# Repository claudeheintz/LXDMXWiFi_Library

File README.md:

# LXDMXWiFi_library
Library for ESP8266 implements Art-Net and sACN with example sketches showing both DMX input to and DMX output from network.

LXDMXWiFi encapsulates functionality for sending and receiving DMX over an ESP8266 WiFi connection
   It is a virtual class with concrete subclasses LXWiFiArtNet and LXWiFiSACN which specifically
   implement the Artistic Licence Art-Net and PLASA sACN 1.31 protocols.

Included examples of the library's use:

         DMX input to network using UART and MAX485 driver chip

         Test of receiving two universes of DMX data from network

         DMX output from network using UART and MAX485 driver chip
            This example includes Eagle files and photos of completed project using this example
            It also includes python script for remote management of protocol/wifi settings
            
Photo shows complete WiFi to DMX unit with RJ45 connector for DMX output: (not to be confused with ethernet)

On the left side is connector for external 5v power and default boot push button.  (holding down default boot forces unit into access point mode allowing configuration via network using python tool.)

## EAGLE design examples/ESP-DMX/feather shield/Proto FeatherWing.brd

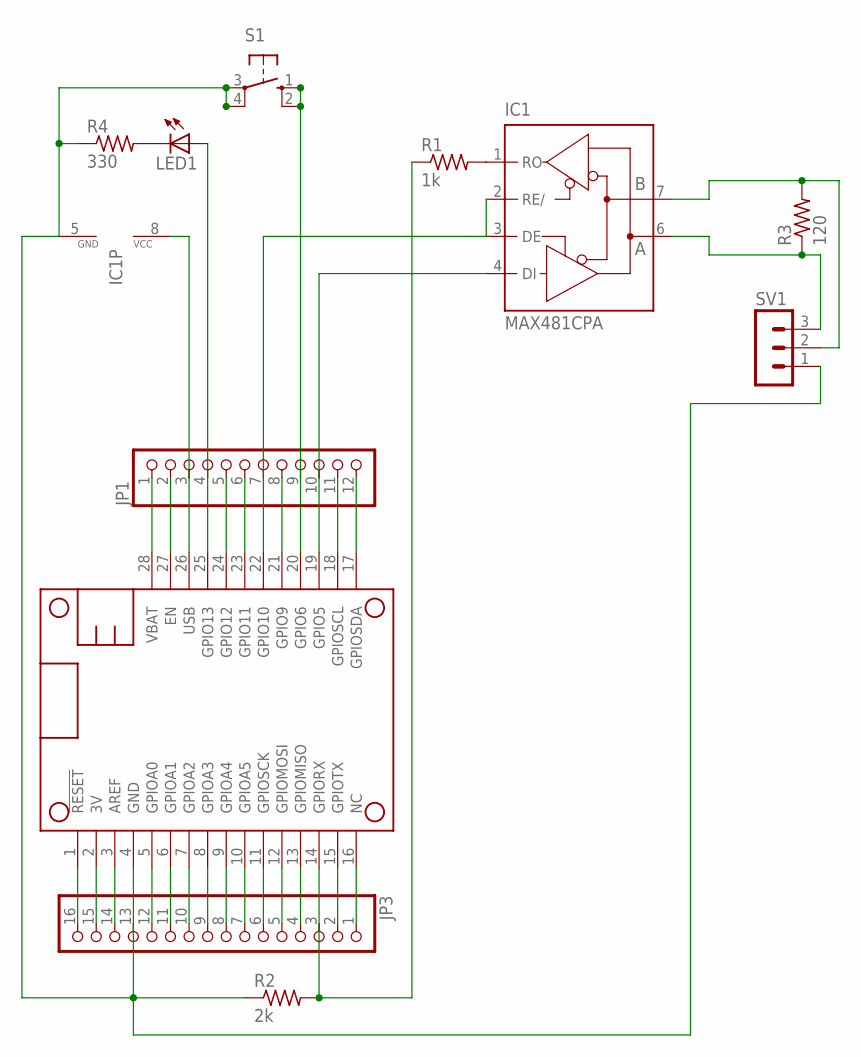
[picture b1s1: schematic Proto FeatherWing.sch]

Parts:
IC1: MAX481CPA; DIL08
JP1: HEADER-1X1276MIL; 1X12_ROUND_76MIL
JP3: HEADER-1X16_76MIL; 1X16_ROUND_76MIL
LED1: LED5MM
MS1: FEATHERWING
R1: 1k; 0204/5
R2: 2k; 0204/5
R3: 120; 0204/5
R4: 330; 0204/5
S1: 10-XX; B3F-10XX
SV1: MA03-1

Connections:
3V: JP3.15, MS1.2 (3V)
AREF: JP3.14, MS1.3 (AREF)
unnamed: JP1.2, MS1.27 (EN)
unnamed: JP3.1, MS1.16 (NC)
unnamed: JP1.4, LED1.A, MS1.25 (GPIO13)
unnamed: JP3.2, MS1.15 (GPIOTX)
unnamed: JP1.5, MS1.24 (GPIO12)
unnamed: JP3.3, MS1.14 (GPIORX), R1.1, R2.2
unnamed: JP3.4, MS1.13 (GPIOMISO)
unnamed: JP3.5, MS1.12 (GPIOMOSI)
unnamed: JP3.6, MS1.11 (GPIOSCK)
unnamed: JP3.7, MS1.10 (GPIOA5)
unnamed: JP3.8, MS1.9 (GPIOA4)
unnamed: JP3.9, MS1.8 (GPIOA3)
unnamed: JP3.10, MS1.7 (GPIOA2)
unnamed: JP3.11, MS1.6 (GPIOA1)
unnamed: JP3.12, MS1.5 (GPIOA0)
unnamed: IC1.1 (RO), R1.2
unnamed: IC1.6 (A), R3.1, SV1.3
unnamed: JP3.16, MS1.1 (!RESET)
unnamed: JP1.6, MS1.23 (GPIO11)
unnamed: IC1.4 (DI), JP1.10, MS1.19 (GPIO5)
unnamed: JP1.8, MS1.21 (GPIO9)
unnamed: JP1.9, MS1.20 (GPIO6), S1.1 (S), S1.2 (S1)
unnamed: LED1.K (C), R4.2
unnamed: JP1.11, MS1.18 (GPIOSCL)
unnamed: JP1.12, MS1.17 (GPIOSDA)
unnamed: IC1.5 (GND), JP3.13, MS1.4 (GND), R2.1, R4.1, S1.3, S1.4 (P1), SV1.1
unnamed: IC1.7 (B), R3.2, SV1.2
unnamed: IC1.2 (RE/), IC1.3 (DE), JP1.7, MS1.22 (GPIO10)
USB: IC1.8 (VCC), JP1.3, MS1.26 (USB)
VBAT: JP1.1, MS1.28 (VBAT)

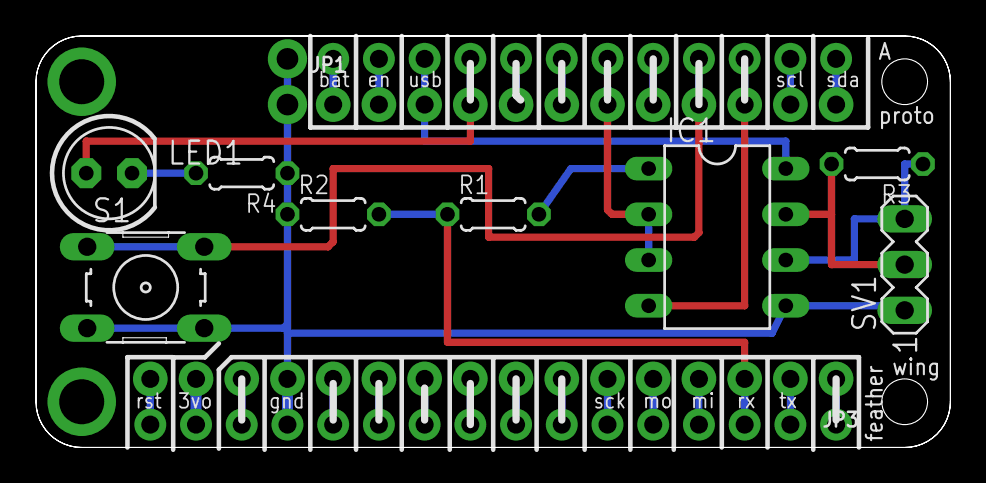
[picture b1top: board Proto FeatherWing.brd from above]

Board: 2 copper layers, 50.8 x 22.9 mm, 11 parts (0 on the bottom side), 32 nets.

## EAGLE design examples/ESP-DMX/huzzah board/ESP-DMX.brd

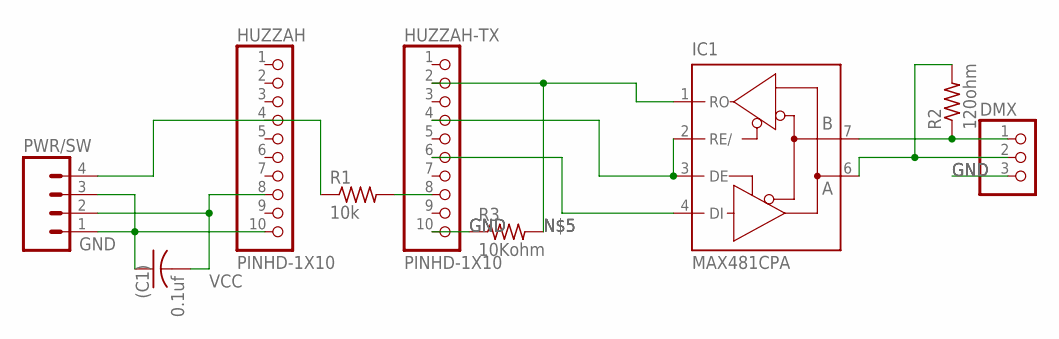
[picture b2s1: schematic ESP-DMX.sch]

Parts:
(C1): 0.1uf; C050-025X075
DMX: PINHD-1X3; 1X03
HUZZAH: PINHD-1X10; 1X10-BIG
HUZZAH-TX: PINHD-1X10; 1X10-BIG
IC1: MAX481CPA; DIL08
PWR/SW: 1X04_HEADER"; 1X04_HEADER
R1: 10k; RESISTOR
R2: 120ohm; RESISTOR
R3: 10Kohm; RESISTOR

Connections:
GND: (C1).1, DMX.3, HUZZAH.10, HUZZAH-TX.10, IC1.5 (GND), PWR/SW.1, PWR/SW.3, R3.1
unnamed: DMX.1, IC1.7 (B), R2.1
unnamed: DMX.2, IC1.6 (A), R2.2
unnamed: HUZZAH-TX.6, IC1.4 (DI)
unnamed: HUZZAH-TX.4, IC1.2 (RE/), IC1.3 (DE)
unnamed: HUZZAH-TX.2, IC1.1 (RO), R3.2
unnamed: HUZZAH-TX.8, R1.2
unnamed: HUZZAH.4, PWR/SW.4, R1.1
VCC: (C1).2, HUZZAH.8, IC1.8 (VCC), PWR/SW.2

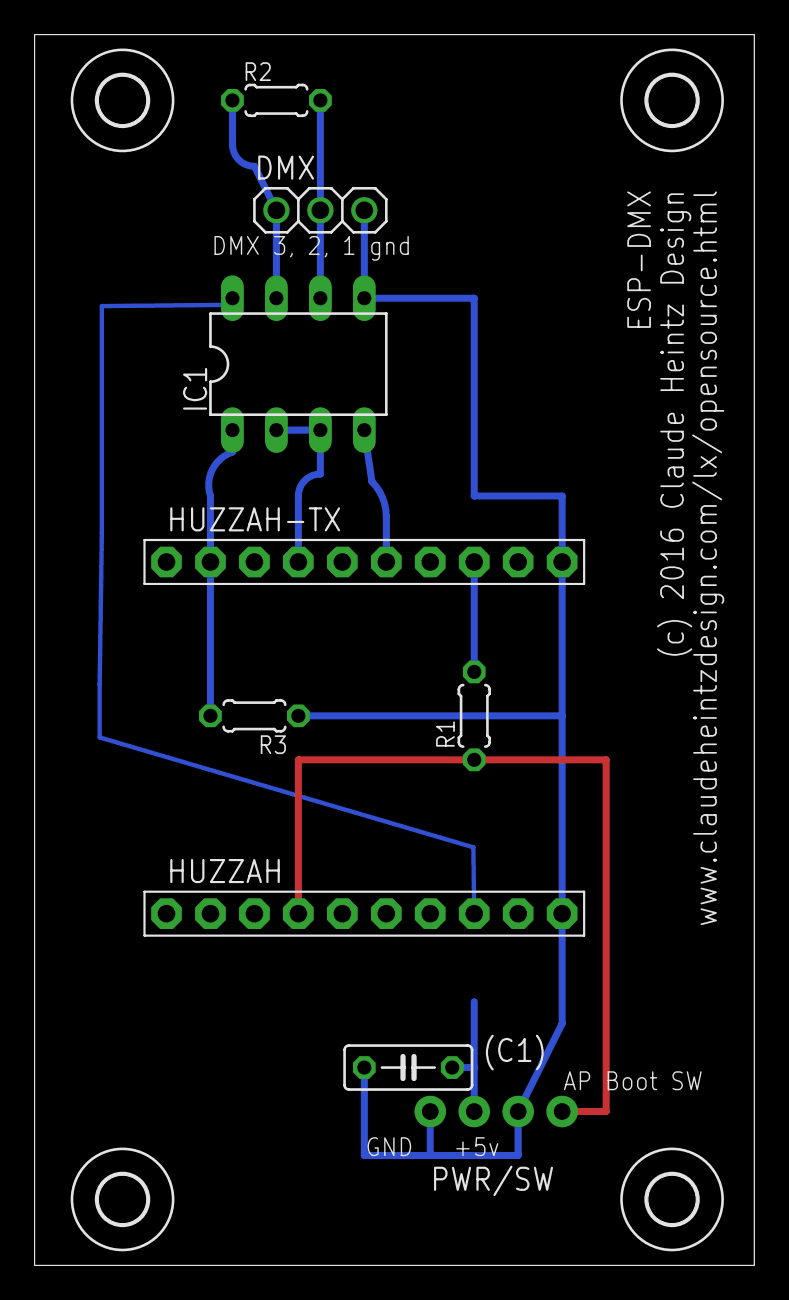
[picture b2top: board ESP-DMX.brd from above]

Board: 2 copper layers, 41.6 x 71.1 mm, 13 parts (0 on the bottom side), 9 nets.

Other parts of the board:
U$3, U$4, U$5, U$6: 2,8

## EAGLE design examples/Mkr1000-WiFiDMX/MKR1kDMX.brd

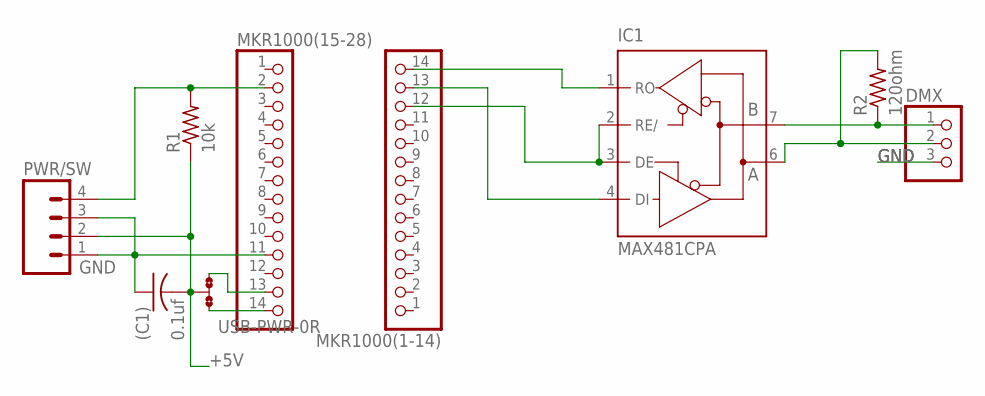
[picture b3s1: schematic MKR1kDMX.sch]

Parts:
(C1): 0.1uf; C050-025X075
DMX: PINHD-1X3; 1X03
IC1: MAX481CPA; DIL08
MKR1000(1-14), MKR1000(15-28): PINHD-1X14; 1X14
PWR/SW: 1X04_HEADER"; 1X04_HEADER
R1: 10k; RESISTOR
R2: 120ohm; RESISTOR
USB-PWR: PWR-IN; B0R-JMP

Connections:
+5V: (C1).2, IC1.8 (VCC), PWR/SW.2, R1.1, USB-PWR.2
GND: (C1).1, DMX.3, IC1.5 (GND), MKR1000(15-28).11, PWR/SW.1, PWR/SW.3
unnamed: DMX.1, IC1.7 (B), R2.1
unnamed: DMX.2, IC1.6 (A), R2.2
unnamed: IC1.4 (DI), MKR1000(1-14).13
unnamed: IC1.2 (RE/), IC1.3 (DE), MKR1000(1-14).12
unnamed: IC1.1 (RO), MKR1000(1-14).14
unnamed: MKR1000(15-28).2, PWR/SW.4, R1.2
unnamed: MKR1000(15-28).13, USB-PWR.3
unnamed: MKR1000(15-28).14, USB-PWR.1

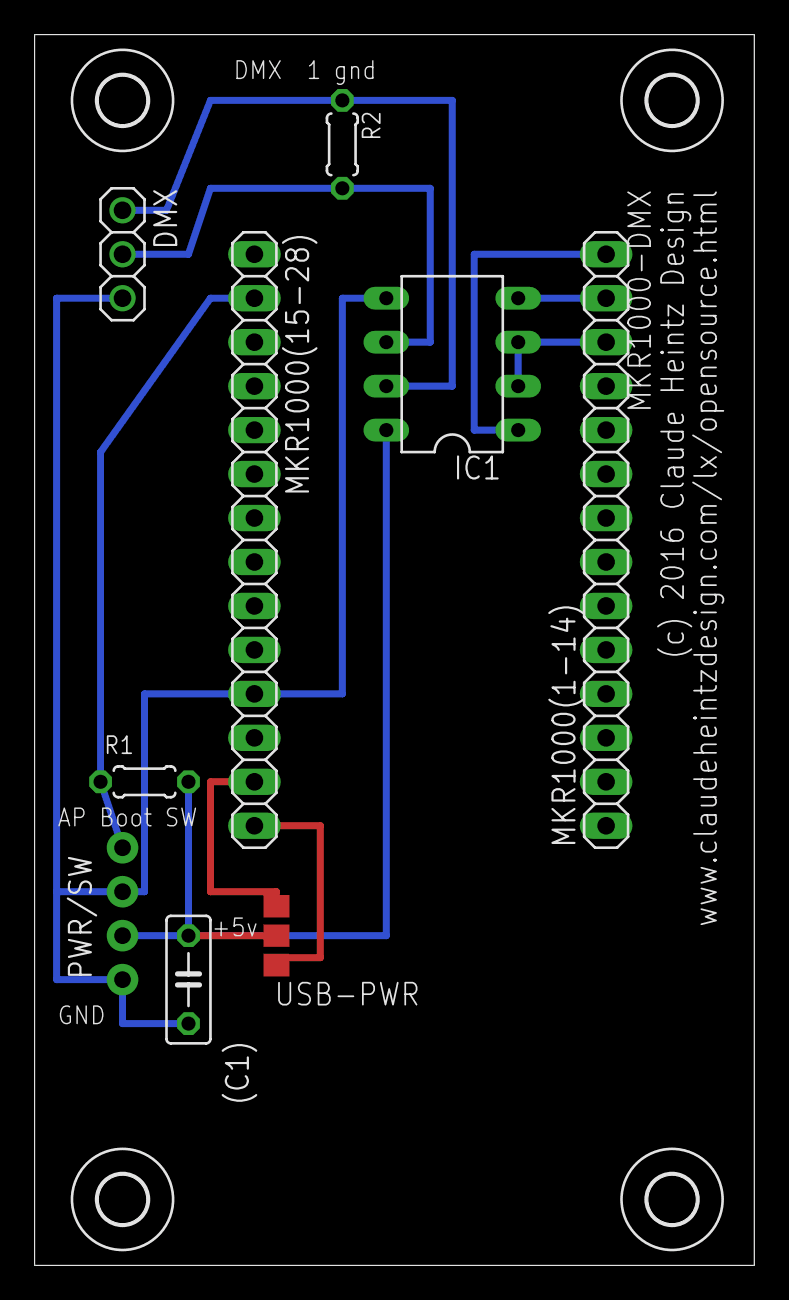
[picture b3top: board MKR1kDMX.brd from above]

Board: 2 copper layers, 41.6 x 71.1 mm, 13 parts (0 on the bottom side), 10 nets.

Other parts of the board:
U$3, U$4, U$5, U$6: 2,8

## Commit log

2015-12-18 improve documentation
2015-12-18 added keywords
2015-12-25 fixed examples
    includes lines showing how to change universe
2016-01-14 improved setup ()
    Fixed a problem with static IP and multicast
2016-01-15 Moved blink while connecting
2016-01-18 updated examples for changes to LXESP8266DMX library
2016-01-25 v1.1 external UDP buffer
    allows use of an external buffer so more than one instance of
    LXWiFiArtNetor LXWiFiSACN can share the same packet data which allows
    for receiving multiple universes
2016-01-26 Expose Art Poll Reply Data
    Places Art-Poll Reply bytes into array that is accessible through
    pointer method. Allows custom poll reply for more than a single
    universe.
2016-01-26 Updates Examples
    Examples are updated for new constant return values. 2 Universe
    example shows custom poll reply
2016-01-31 static _reply_buffer
2016-02-12 Fixed Initialize
    missing _dmx_slots_a = 0; _dmx_slots_b = 0;
2016-04-01 v2 with remote config
    Adds remote configuration for WiFi2DMX.
    Adds Eagle files for WiFi2DMX
2016-04-06 added photos
    photos show completed projects
2016-04-06 update read
2016-04-13 Remote Management
    Improvements in remote management and support of Art-Net ArtAddress
    functions
2016-04-16 updated config utility
    Updated config utility for WiFi2DMX example
2016-04-17 added Mac version to example config utility
2016-04-18 Added Example
    Added combined input/output remote configurable example
2016-04-21 refactor WiFiUDP
    Refactored includes changing from WiFiUDP.h to Udp.h and passing
    pointer to generic UDP object. Allows use with WiFi101 library, except
    for Multicast (see WiFiDMX.h)
2016-04-22 Move config to header
    Moved LXDMXWiFiConfig to separate header file (in ESP-DMX example
    folder)
2016-04-22 update ESP-DMX example
    moved ESP-DMX example LXDMXWiFiConfig to separate file
2016-04-22 Add MKR1000 example
    Must comment out lines in library src/LXDMXWiFi.h to be compatible with
    WiFi101 library.
2016-04-22 add photo
2016-04-22 uncomment
    These lines need to be commented out for WiFi101 compatibility.
2016-04-23 update example
    moved remote config to separate header
2016-04-23 fixed examples
    Fixed examples for removing remote config to separate header/cpp files
2016-04-24 update examples
2016-04-25 refactor config
    Encapsulates remote config into class (DMXWiFiConfig object). Includes
    all functions including reading and writing config to EEPROM
2016-04-28 Update Example
    Updates remote configuration examples Java utility
2016-05-03 update examples
    also updates library properties for samd for Mkr1000. (still need to
    comment out lines to be compatible with WiFi101 library)
2016-05-03 updated examples
    Added ESP8266 NeoPixel example
2016-05-04 Compatibility with WiFi101
    Finally able to conditionally include files. Library should now work
    without commenting out lines in LXWiFiDMX.h (using the latest IDE)
2016-05-14 update NeoPixel Example
    Adds check so that total_pixels does not exceed 512.
2016-05-25 update NeoPixel Example
2016-05-29 improve config utility example
    Adds an html file describing config utility use.
2016-05-31 example LXDMXWiFiConfig.cpp
    Update example LXDMXWiFiConfig.cpp
2016-06-10 update Serial baud
2016-06-23 Dual Protocol Support
    Updated examples to support listening for both Art-Net and sACN,
    merging sources HTP. Also includes improvements to remote
    configuration.
2016-06-23 Update Windows App
2016-07-12 fix Art-Net mfg code
2016-10-04 fix IP address in poll rely
2016-10-15 fixes argument type
    index should be uint16_t
2016-10-22 Update Art-Net Credit
2016-11-13 Improved Art-Net Support
2016-11-18 Update Library Source
    Improves Art-Net Port-Address and sACN universe handling, supporting
    the full range.
    Improves Art-Net support in general.
2016-11-19 fix config header
2017-01-26 Misc Fixes and Refinements
    Most critical is an overflow check on the packet buffer when merging
    two sources of Art-Net
2017-03-31 Change input pullup resistor
2017-04-12 New Adafruit Feather Example
    Inspired by AdaBox 3
2017-04-17 Add activity LED
2017-06-26 Add ESP32 example
2017-09-19 add rdm support
2017-09-19 update configuration utility for RDM option
2017-09-21 Add support for ArtCommand opcode
2017-09-22 clarify IPAddress for ArtPollReply and broadcast
2017-09-22 fix deletion
2017-09-27 update example
2017-09-28 fix ArtCommand and feather example
2017-10-11 update MKR 1000 example for RDM
2017-10-26 add support for sACN priority
2017-10-29 update properties
2017-10-31 Change ESP32 example for RDM
2017-11-05 update example for improved ESP32DMX library
2018-01-02 Update ESP32 example
    Update examples
2018-01-03 add ArtPoll reply for input mode
2018-01-11 Don't break older code...
2018-01-12 make remote configuration optional (off by default)
2018-01-12 make remote configuration optional (update example)
2018-01-16 add broadcast address to search in Java config utility
2018-01-16 update example config utility
2018-02-22 Update Adafruit ESP32 Feather Example
2018-06-18 Simple indent mode
2018-06-19 Set ArtPoll mode
2018-06-19 add ArtAddress and ArtCMD to readArtPollPacketContents
2018-06-19 rename readArtPollPacket as readArtNetPacketInputMode to make useage more apparent
2018-06-19 update example showing use of readArtNetPacketInputMode
2018-06-19 check config packet in input mode only when macro defined
2018-06-19 update additional examples
2018-08-22 update example Serial.begin() not compatible with dmx
2018-09-05 Update feather board design for example
2019-01-17 update comments with EEPROM instructions
2019-04-11 Untested: Remove zero equality check to fix compile error
2019-04-11 Fix ArtNet source address check
2019-04-11 clarify INADDR_ANY and INADDR_NONE 0, -1 respectively
2019-04-12 add define of INADDR_ANY for ESP32 compatibility
2020-02-21 add Art-Net poll sending
2020-02-21 add Art-Net poll reply callback for input mode
2020-12-28 update examples including new for Wio Terminal
2021-01-10 refactor neo pixels example
2021-01-16 add simple RGB PWM example
2021-01-16 fix comments in main file.
2021-11-16 add casts to allow compilation with versions of ESP32 board packages
2022-11-02 update ESP32 example localIP() returns 0.0.0.0 in AP mode
2022-11-02 corrects use of softAPIP() in esp32 example
2025-11-25 Adjust loop range for clearing reply buffer

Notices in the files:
examples/ESP-DMX/huzzah board/ESP-DMX.brd:
(c) 2016 Claude Heintz Design
